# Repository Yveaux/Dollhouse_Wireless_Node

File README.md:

# Dollhouse Wireless nRF24 MySensors IoT node

This sensor node was designed to be used in the MySensors dollhouse display, created for the [Eindhoven Maker Faire 2017](http://www.eindhovenmakerfaire.nl)

Left-to-right: gesture sensor, door sensor, wind sensor, soil moisture sensor

Original requirements
========
* Very small, so it can be mounted visible in the house without distracting too much 
* 5V supply, or battery powered (CR2032)
* runs at 3V3
* nRF24L01+, SMD version
* 8MHz, internal oscillator
* Optional buffer cap (47..100uF) for battery node
* ATMega328; cheap, stay close to well known Arduino UNO/Pro mini
* ISP connector; small, ProtoProg
* Serial connector; small, pogo pins, GND, RX, TX, DTR (reset)
* At least 1 sensor per node
* On/off switch (for battery sensors)
* Application LED (Pin 4)
* Power LED (d.n.p. for battery sensor)
* IO to support sensors

The resulting node is very small (28.5 x 25.5mm, excluding antenna) and costs roughly E4,30/piece (excluding sensor)

Layout
========

Addon connector pinout
========
| Pin  | Arduino Pin | Alternate Function |
| ---- | --- | --- |
| 1    | GND | | |
| 2    | VCC |
| 3    | 3 | INT1 |
| 4    | 2 | INT0 |
| 5    | A5 | I2C SCL |
| 6    | A4 | I2C SDA |
| 7    | 5 | |
| 8    | 6 | |
| 9    | 7 | |
| 10   | 8 | |

Pin 1 is next to the FTDI pogo pin connector.

Addon board
========
I created a small addon board to simplify connecting a numer of standard sensors. It can be mounted on the IO connector using male headers.
Supported sensors/actuators:
* 2 servo's
* AM312 Mini PIR
* BME280 Temperature, relative humidty & pressure sensor
* APDS9930 Digital Ambient Light and Proximity Sensor
* APDS9960 RGB & gesture sensor
Please make sure to verify the pinout and supply level of a module before connecting it to the addon board!

Addon proto board
========
Small 10 x 4 proto board to connect other sensors (e.g. the soil humidity & wind-speed reed sensor)

Construction
========
Start with the ATMega, followed by the small SMD's on the top and nRF24. Flip the board and mount either the CR2032 holder, or the AMS1117-3V3.

The switch is optional. Either mount the switch or short solder jumper SJ1.

Mount the power LED (and its resistor R2) if you prefer a visible indication of a node being switched on. Do not mount it on a CR2032 powered sleeping node as it will drain the battery too quickly.

Pull-up resistors R4-R11 can be used for digital inputs to further reduce the power drain. Mount approx. 1Meg ohm and disable internal pullups.

When powered from a 5V supply (and AMS1117 mounted) use the RAW and GND pins to power the board.

Programming
========
To keep the sensor small the ISP and FTDI connectors are scaled down to use pogo pins for programming.
ISP programming requires a [ProtoProg](http://protofusion.org/wordpress/2013/05/open-hardware-pogo-pin-programmer/) adapter.

To flash the bootloader refer to my [Ikea Molgan Hack](https://github.com/Yveaux/Ikea_Molgan_Hack)

The serial connection used by the Arduino IDE is available at a 5 pin FTDI-to-pogo adapter, also included in this repository. Make sure to align the white pin on the adapter to the white pin on the board. I use the node's power when programming at 3V3 serial levels.

Known issues
========
* The buffer capacitor C4 is located after the switch. Powering off a sleeping sensor will take some to actually shut down the sensor as the buffer capacitor will still supply the ATMega for some time.

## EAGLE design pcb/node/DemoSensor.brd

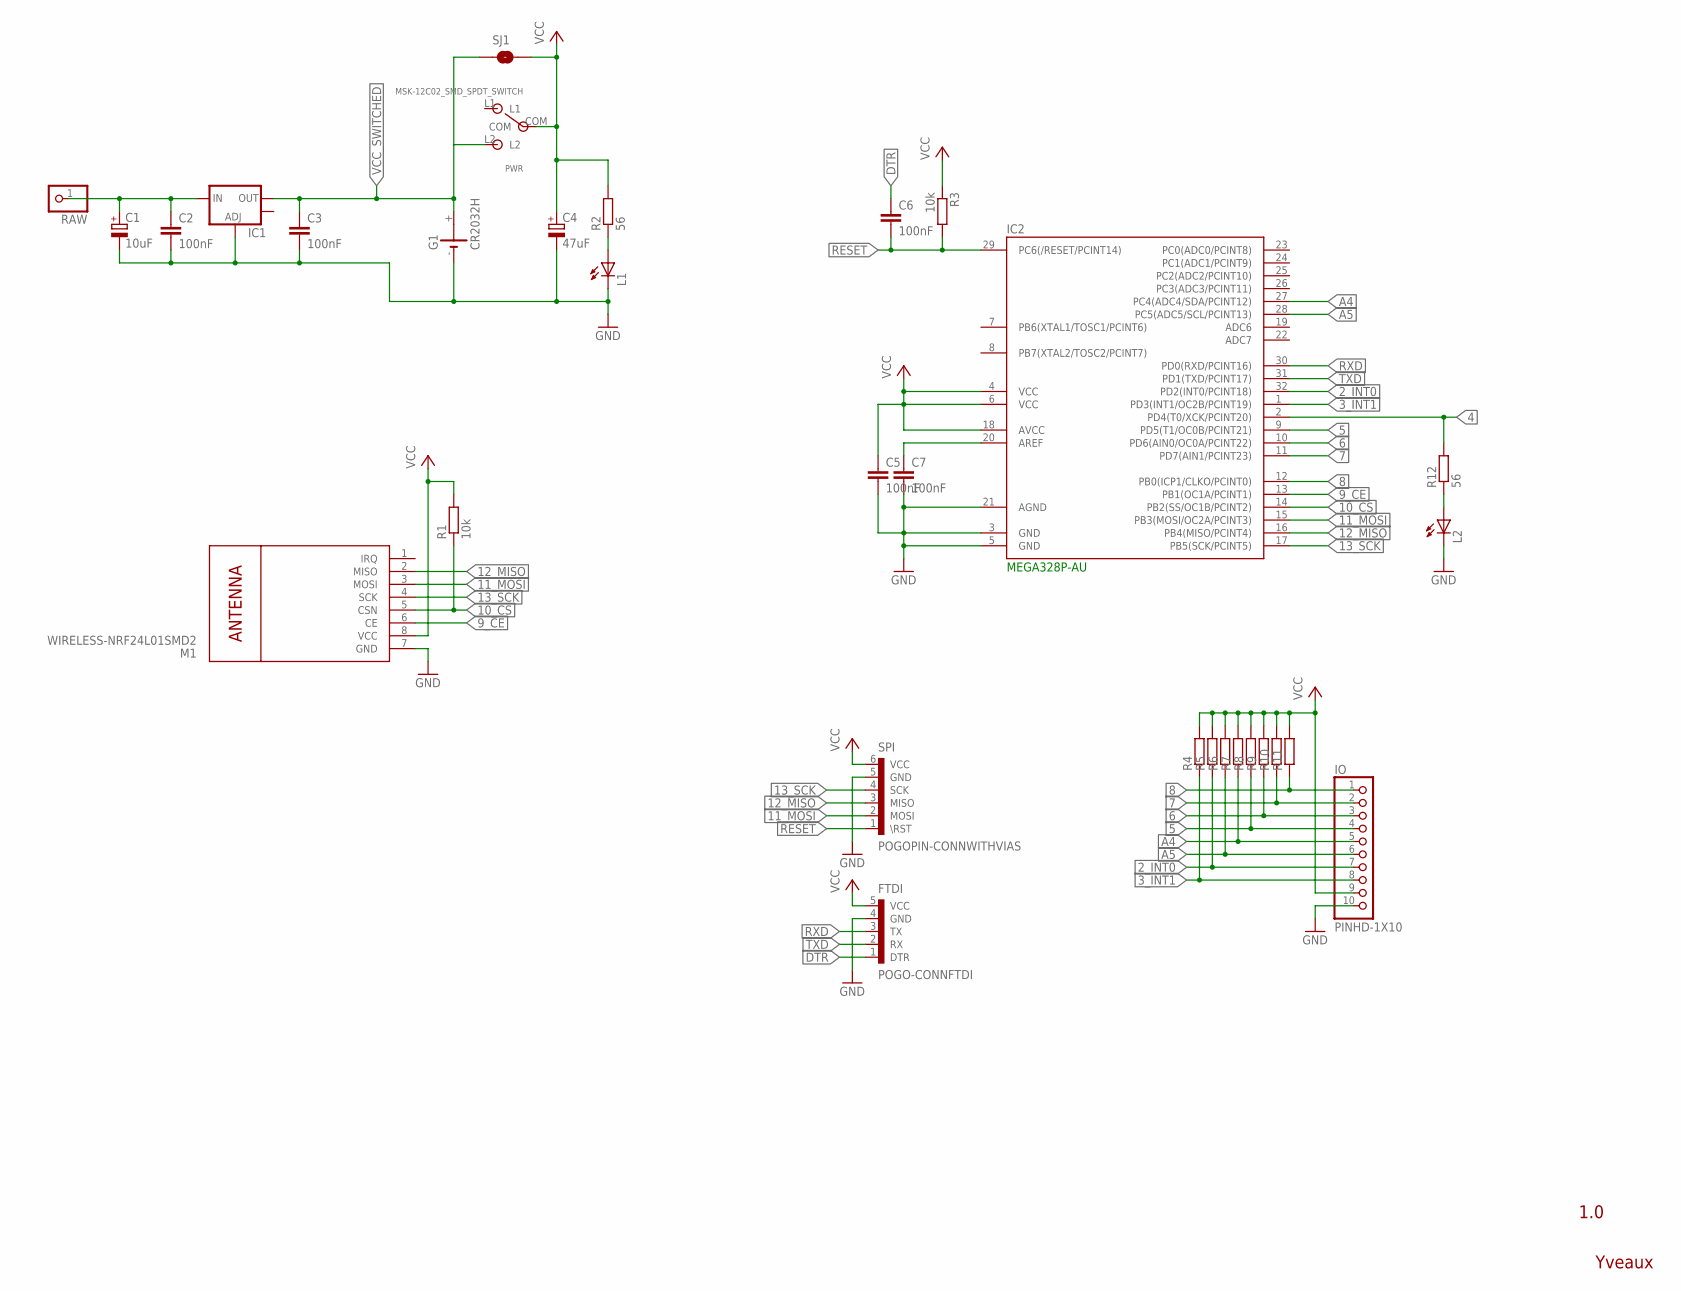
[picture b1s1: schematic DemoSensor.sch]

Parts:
C1: 10uF; SMC_A
C2, C3, C5, C6, C7: 100nF; C0603
C4: 47uF; SMC_A
FTDI: POGO-CONNFTDI; POGO5-VIAS
G1: CR2032H
IC1: V_REG_LM1117SOT223; SOT223
IC2: MEGA328P-AU; TQFP32-08
IO: PINHD-1X10; 1X10-BIG
L1, L2: LEDCHIPLED_0603; CHIPLED_0603
M1: WIRELESS-NRF24L01SMD2; WIRELESS-NRF24L01-SMD-2
PWR: MSK-12C02_SMD_SPDT_SWITCH; MSK-12C02
R1, R3: 10k; R0603
R2, R12: 56; R0603
R4, R5, R6, R7, R8, R9, R10, R11: R-EU_R0603; R0603
RAW: PINHD-1X1; 1X01
SJ1: SOLDERJUMPERNO; SJ_2S-NO
SPI: POGOPIN-CONNWITHVIAS; POGOPROG-CONN-0H

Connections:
2_INT0: IC2.32 (PD2(INT0/PCINT18)), IO.7, R5.1
3_INT1: IC2.1 (PD3(INT1/OC2B/PCINT19)), IO.8, R4.1
4: IC2.2 (PD4(T0/XCK/PCINT20)), R12.2
5: IC2.9 (PD5(T1/OC0B/PCINT21)), IO.4, R8.1
6: IC2.10 (PD6(AIN0/OC0A/PCINT22)), IO.3, R9.1
7: IC2.11 (PD7(AIN1/PCINT23)), IO.2, R10.1
8: IC2.12 (PB0(ICP1/CLKO/PCINT0)), IO.1, R11.1
9_CE: IC2.13 (PB1(OC1A/PCINT1)), M1.6 (CE)
10_CS: IC2.14 (PB2(SS/OC1B/PCINT2)), M1.5 (CSN), R1.1
11_MOSI: IC2.15 (PB3(MOSI/OC2A/PCINT3)), M1.3 (MOSI), SPI.2 (MOSI)
12_MISO: IC2.16 (PB4(MISO/PCINT4)), M1.2 (MISO), SPI.3 (MISO)
13_SCK: IC2.17 (PB5(SCK/PCINT5)), M1.4 (SCK), SPI.4 (SCK)
A4: IC2.27 (PC4(ADC4/SDA/PCINT12)), IO.5, R7.1
A5: IC2.28 (PC5(ADC5/SCL/PCINT13)), IO.6, R6.1
DTR: C6.1, FTDI.1 (DTR)
GND: C1.-, C2.2, C3.2, C4.-, C5.2, C7.2, FTDI.4 (GND), G1.-, IC1.1 (ADJ), IC2.3 (GND), IC2.5 (GND), IC2.21 (AGND), IO.10, L1.C, L2.C, M1.7 (GND), SPI.5 (GND)
unnamed: L2.A, R12.1
unnamed: L1.A, R2.1
unnamed: C7.1, IC2.20 (AREF)
RAW: C1.+, C2.1, IC1.3 (IN), RAW.1
RESET: C6.2, IC2.29 (PC6(/RESET/PCINT14)), R3.2, SPI.1 (\RST)
RXD: FTDI.3 (TX), IC2.30 (PD0(RXD/PCINT16))
TXD: FTDI.2 (RX), IC2.31 (PD1(TXD/PCINT17))
VCC: C4.+, C5.1, FTDI.5 (VCC), IC2.4 (VCC), IC2.6 (VCC), IC2.18 (AVCC), IO.9, M1.8 (VCC), PWR.COM, R1.2, R2.2, R3.1, R4.2, R5.2, R6.2, R7.2, R8.2, R9.2, R10.2, R11.2, SJ1.2, SPI.6 (VCC)
VCC_SWITCHED: C3.1, G1.+, IC1.2 (OUT), PWR.L2, SJ1.1

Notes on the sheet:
1.0
Yveaux

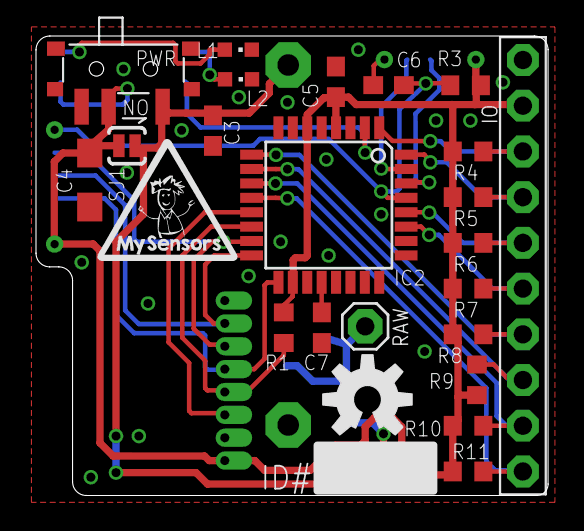
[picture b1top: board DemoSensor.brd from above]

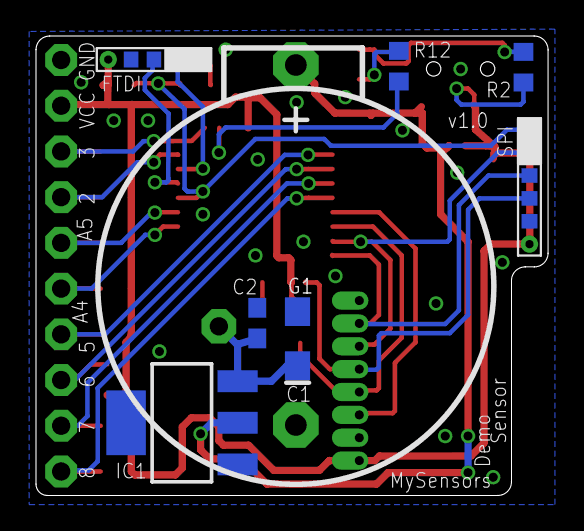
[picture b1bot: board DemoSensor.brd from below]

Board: 2 copper layers, 28.4 x 25.5 mm, 33 parts (8 on the bottom side), 25 nets.

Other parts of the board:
U$5: OSHW-LOGO-M
U$6: STICKER_8MM

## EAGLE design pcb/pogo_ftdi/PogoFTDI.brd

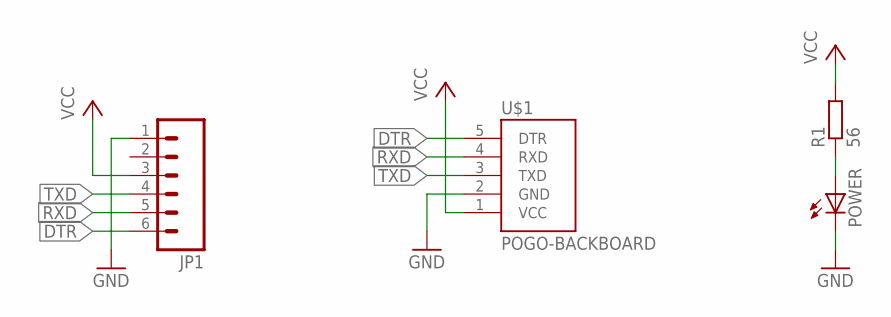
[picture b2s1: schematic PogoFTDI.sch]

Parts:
JP1: M06SIP; 1X06
POWER: LEDCHIPLED_0603; CHIPLED_0603
R1: 56; R0603
U$1: POGO-BACKBOARD; POGO5-BACKMOUNT

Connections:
DTR: JP1.6, U$1.5 (DTR)
GND: JP1.1, POWER.C, U$1.2 (GND)
unnamed: POWER.A, R1.1
RXD: JP1.5, U$1.4 (RXD)
TXD: JP1.4, U$1.3 (TXD)
VCC: JP1.3, R1.2, U$1.1 (VCC)

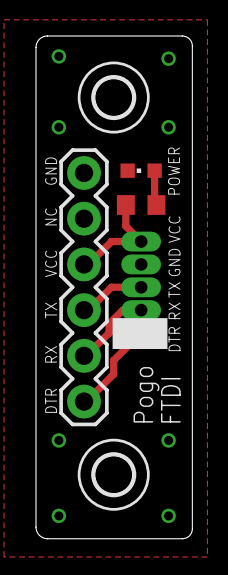
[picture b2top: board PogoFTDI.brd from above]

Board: 2 copper layers, 8.7 x 27.9 mm, 6 parts (0 on the bottom side), 6 nets.

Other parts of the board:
U$2, U$3: HOLE_M2PAN_TIGHT

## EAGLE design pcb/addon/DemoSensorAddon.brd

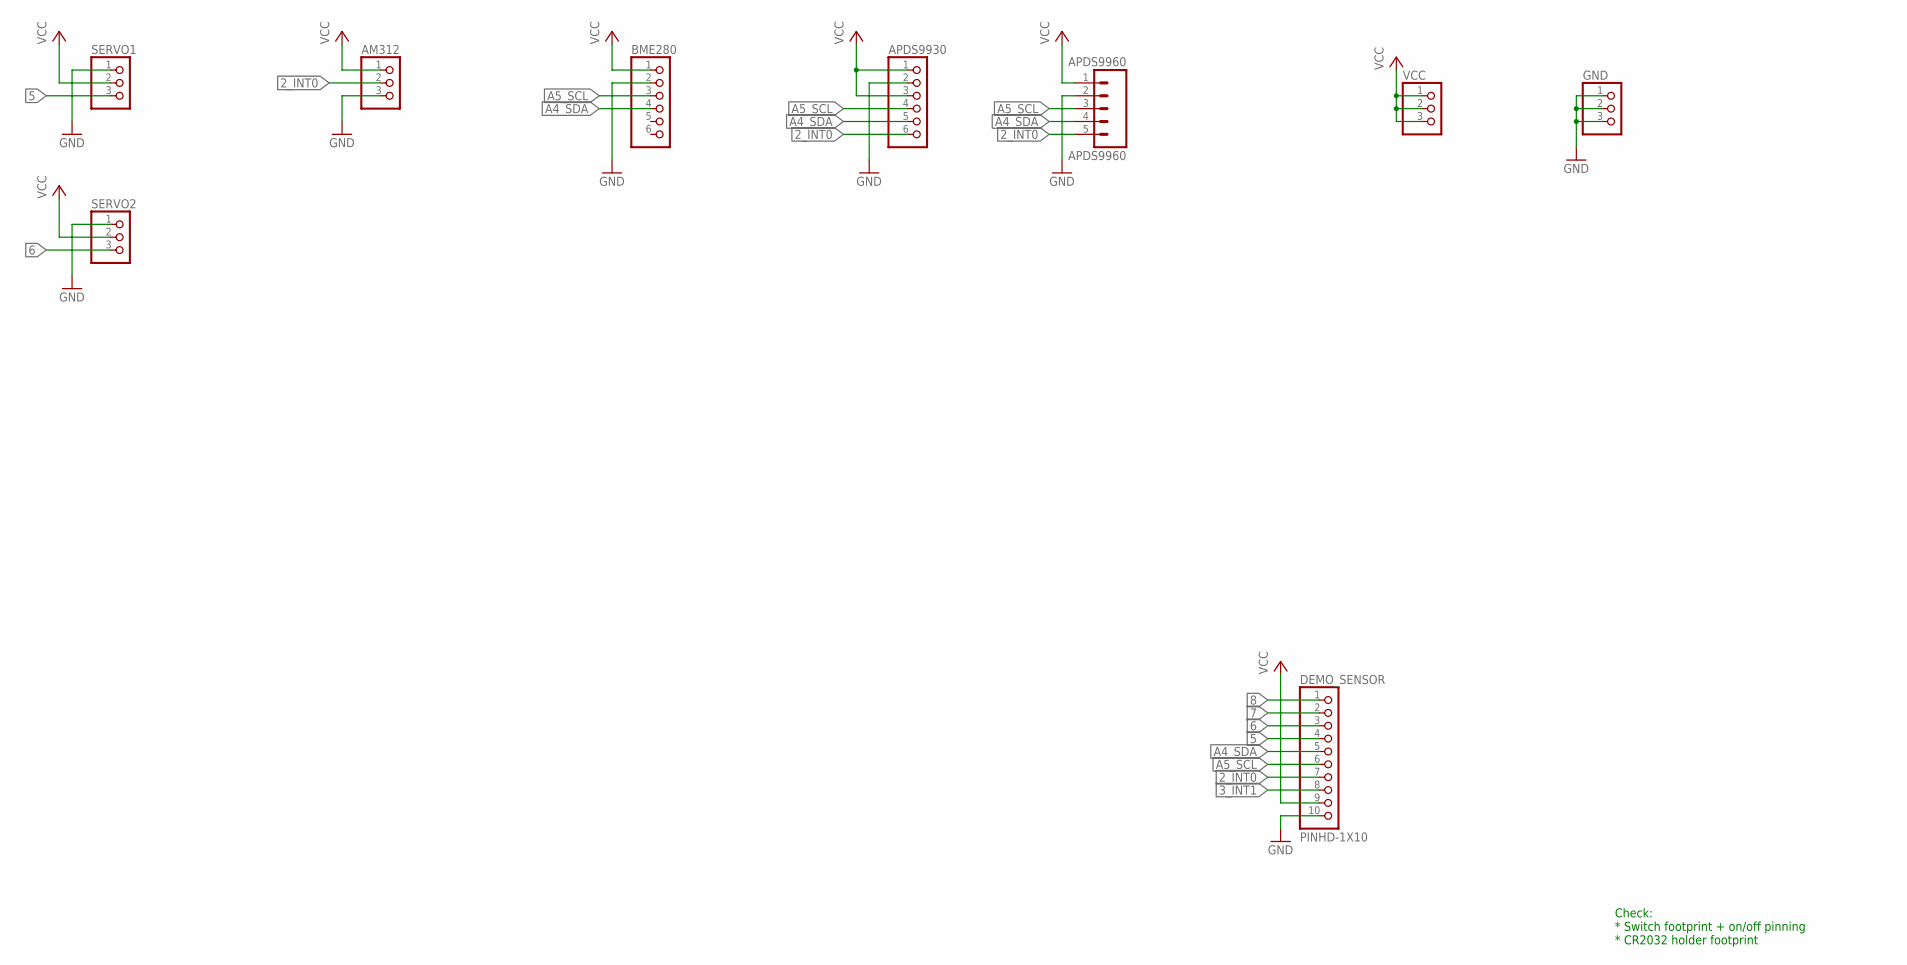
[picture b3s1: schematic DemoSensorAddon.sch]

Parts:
AM312: PINHD-1X3; 1X03
APDS9930: PINHD-1X6; 1X06
APDS9960: APDS9960; 1X05
BME280: PINHD-1X6; 1X06
DEMO_SENSOR: PINHD-1X10; 1X10-BIG
GND: PINHD-1X3; 1X03
SERVO1, SERVO2: PINHD-1X3; 1X03
VCC: PINHD-1X3; 1X03

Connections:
2_INT0: AM312.2, APDS9930.6, APDS9960.5, DEMO_SENSOR.7
3_INT1: DEMO_SENSOR.8
5: DEMO_SENSOR.4, SERVO1.3
6: DEMO_SENSOR.3, SERVO2.3
7: DEMO_SENSOR.2
8: DEMO_SENSOR.1
A4_SDA: APDS9930.5, APDS9960.4, BME280.4, DEMO_SENSOR.5
A5_SCL: APDS9930.4, APDS9960.3, BME280.3, DEMO_SENSOR.6
GND: AM312.3, APDS9930.2, APDS9960.2, BME280.2, DEMO_SENSOR.10, GND.1, GND.2, GND.3, SERVO1.1, SERVO2.1
VCC: AM312.1, APDS9930.1, APDS9930.3, APDS9960.1, BME280.1, DEMO_SENSOR.9, SERVO1.2, SERVO2.2, VCC.1, VCC.2, VCC.3

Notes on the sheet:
Check: * Switch footprint + on/off pinning * CR2032 holder footprint

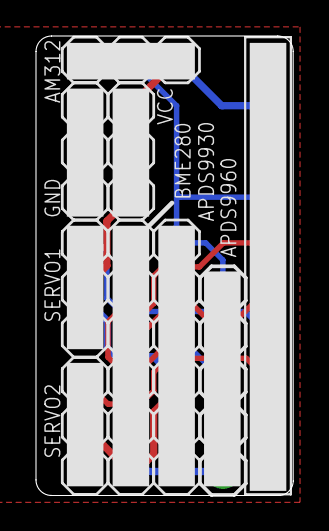
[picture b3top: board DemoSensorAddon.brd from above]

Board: 2 copper layers, 14.3 x 25.5 mm, 9 parts (0 on the bottom side), 7 nets.

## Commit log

2017-09-09 Add design files & gerbers
2017-09-09 Add images
2017-09-09 Scaled bottom pcb image
2017-09-09 Added BOM
2017-09-14 Added pinout table
2020-08-03 Fix pin 2 & 3 swap

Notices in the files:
parts and their libraries:
SparkFun: Licensing: CC v3.0 Share-Alike You are welcome to use this library for commercial purposes.
SparkFun-Aesthetics: Licensing: Creative Commons ShareAlike 4.0 International - https://creativecommons.org/licenses/by-sa/4.0
